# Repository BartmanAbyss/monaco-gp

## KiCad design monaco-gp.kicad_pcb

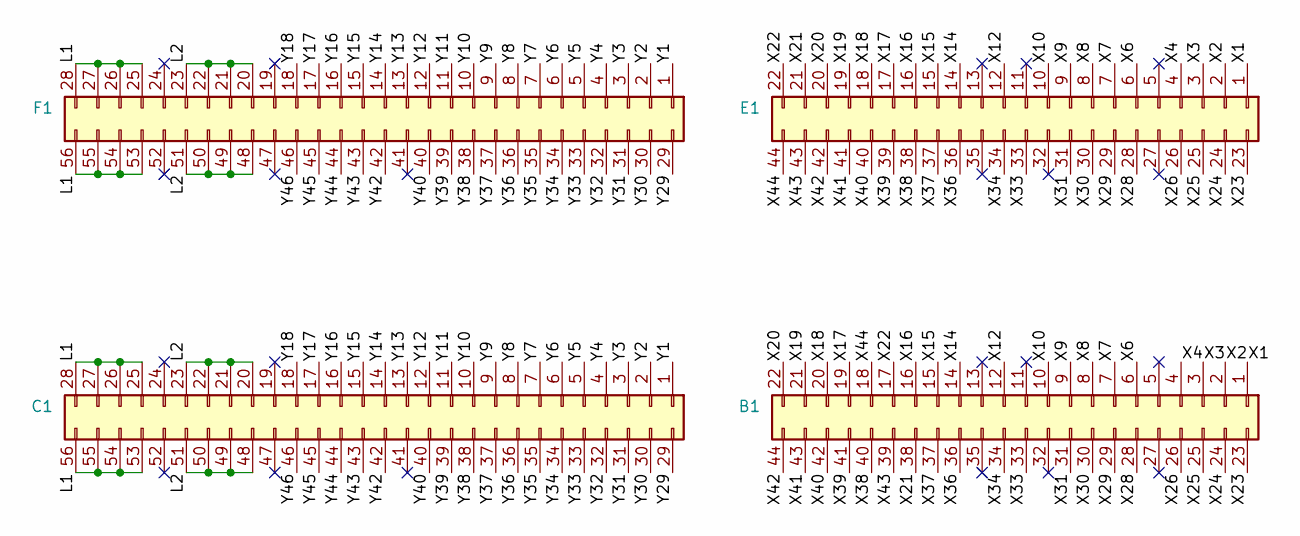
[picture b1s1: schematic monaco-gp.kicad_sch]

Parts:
B1: Conn_02x22_Top_Bottom; Edge2x22_3.95mm_bottom
C1: Conn_02x28_Top_Bottom; Edge2x28_3.95mm_top
E1: Conn_02x22_Top_Bottom; Edge2x22_3.95mm_top
F1: Conn_02x28_Top_Bottom; Edge2x28_3.95mm_bottom

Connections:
/L1: C1.25, C1.26, C1.27, C1.28, C1.53, C1.54, C1.55, C1.56, F1.25, F1.26, F1.27, F1.28, F1.53, F1.54, F1.55, F1.56
/L2: C1.20, C1.21, C1.22, C1.23, C1.48, C1.49, C1.50, C1.51, F1.20, F1.21, F1.22, F1.23, F1.48, F1.49, F1.50, F1.51
/X1: B1.1, E1.1
/X2: B1.2, E1.2
/X3: B1.3, E1.3
/X4: B1.4, E1.4
/X6: B1.6, E1.6
/X7: B1.7, E1.7
/X8: B1.8, E1.8
/X9: B1.9, E1.9
/X10: B1.10, E1.10
/X12: B1.12, E1.12
/X14: B1.14, E1.14
/X15: B1.15, E1.15
/X16: B1.16, E1.16
/X17: B1.19, E1.17
/X18: B1.20, E1.18
/X19: B1.21, E1.19
/X20: B1.22, E1.20
/X21: B1.38, E1.21
/X22: B1.17, E1.22
/X23: B1.23, E1.23
/X24: B1.24, E1.24
/X25: B1.25, E1.25
/X26: B1.26, E1.26
/X28: B1.28, E1.28
/X29: B1.29, E1.29
/X30: B1.30, E1.30
/X31: B1.31, E1.31
/X33: B1.33, E1.33
/X34: B1.34, E1.34
/X36: B1.36, E1.36
/X37: B1.37, E1.37
/X38: B1.40, E1.38
/X39: B1.41, E1.39
/X40: B1.42, E1.40
/X41: B1.43, E1.41
/X42: B1.44, E1.42
/X43: B1.39, E1.43
/X44: B1.18, E1.44
/Y1: C1.1, F1.1
/Y2: C1.2, F1.2
/Y3: C1.3, F1.3
/Y4: C1.4, F1.4
/Y5: C1.5, F1.5
/Y6: C1.6, F1.6
/Y7: C1.7, F1.7
/Y8: C1.8, F1.8
/Y9: C1.9, F1.9
/Y10: C1.10, F1.10
/Y11: C1.11, F1.11
/Y12: C1.12, F1.12
/Y13: C1.13, F1.13
/Y14: C1.14, F1.14
/Y15: C1.15, F1.15
/Y16: C1.16, F1.16
/Y17: C1.17, F1.17
/Y18: C1.18, F1.18
/Y29: C1.29, F1.29
/Y30: C1.30, F1.30
/Y31: C1.31, F1.31
/Y32: C1.32, F1.32
/Y33: C1.33, F1.33
/Y34: C1.34, F1.34
/Y35: C1.35, F1.35
/Y36: C1.36, F1.36
/Y37: C1.37, F1.37
/Y38: C1.38, F1.38
/Y39: C1.39, F1.39
/Y40: C1.40, F1.40
/Y42: C1.42, F1.42
/Y43: C1.43, F1.43
/Y44: C1.44, F1.44
/Y45: C1.45, F1.45
/Y46: C1.46, F1.46

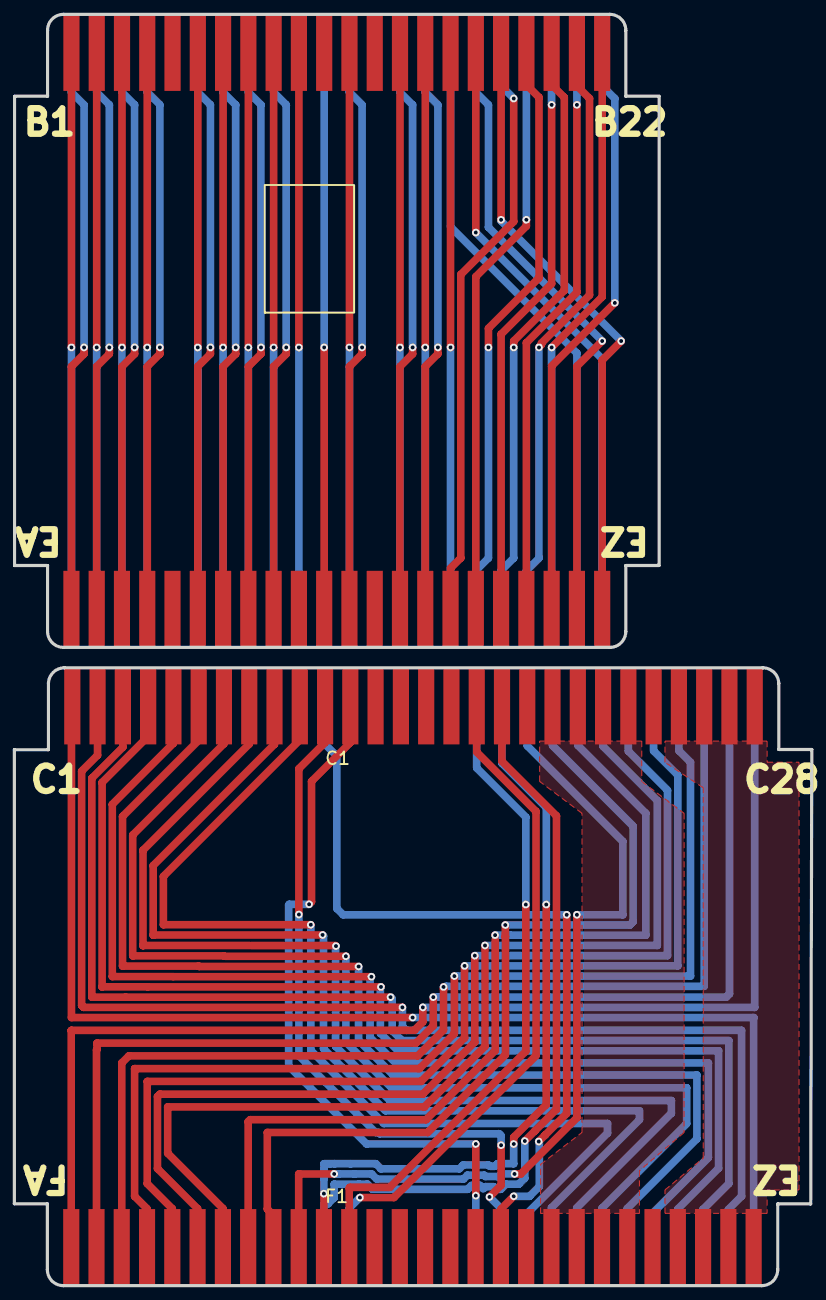
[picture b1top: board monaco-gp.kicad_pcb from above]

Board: 2 copper layers, 124.9 x 199.2 mm, 4 parts (0 on the bottom side), 75 nets.

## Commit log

2025-07-01 initial commit. B-to-E is wrong
2025-07-07 correct footprints in schematic
2025-07-07 footprints based on photos
2025-07-07 routing
2025-07-28 fixed footprints again. 22-pin board should be okay now :)
2025-07-28 split connectors into 2 projects/PCBs generate new gerbers
2025-08-01 cleanup, add holes, shrink connector size
